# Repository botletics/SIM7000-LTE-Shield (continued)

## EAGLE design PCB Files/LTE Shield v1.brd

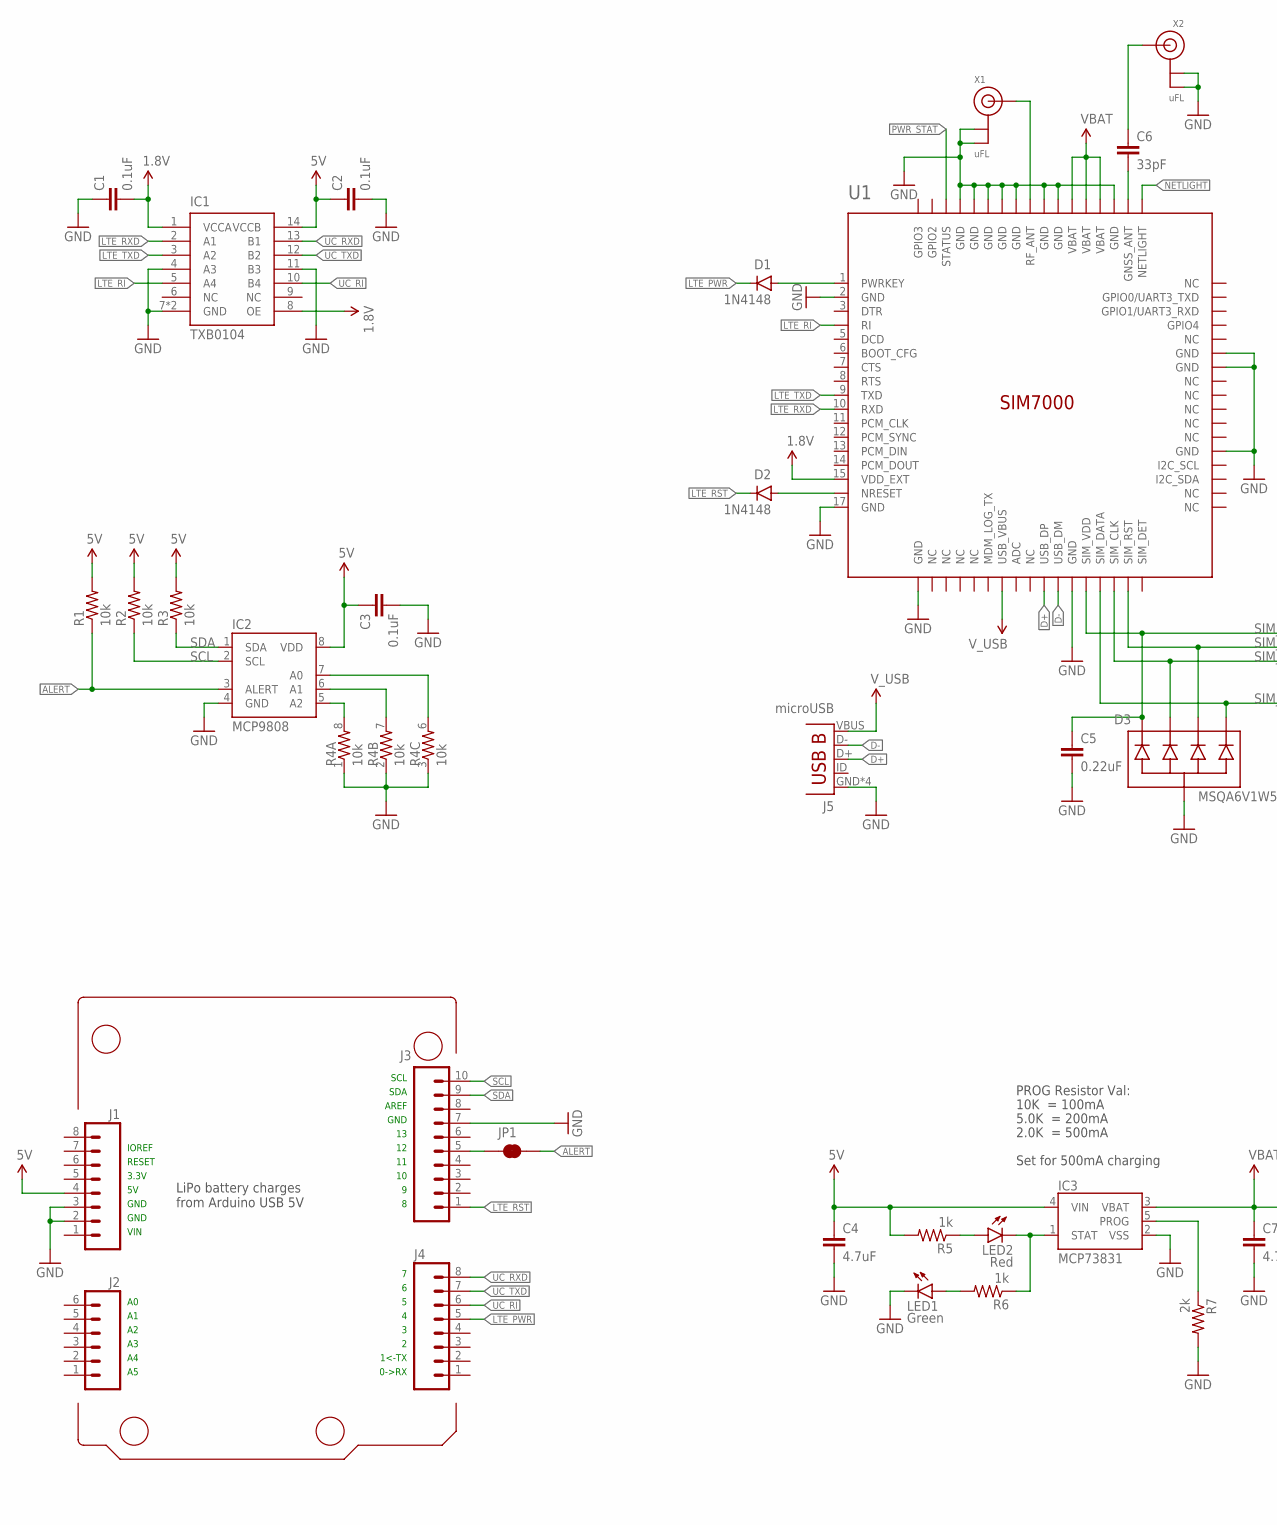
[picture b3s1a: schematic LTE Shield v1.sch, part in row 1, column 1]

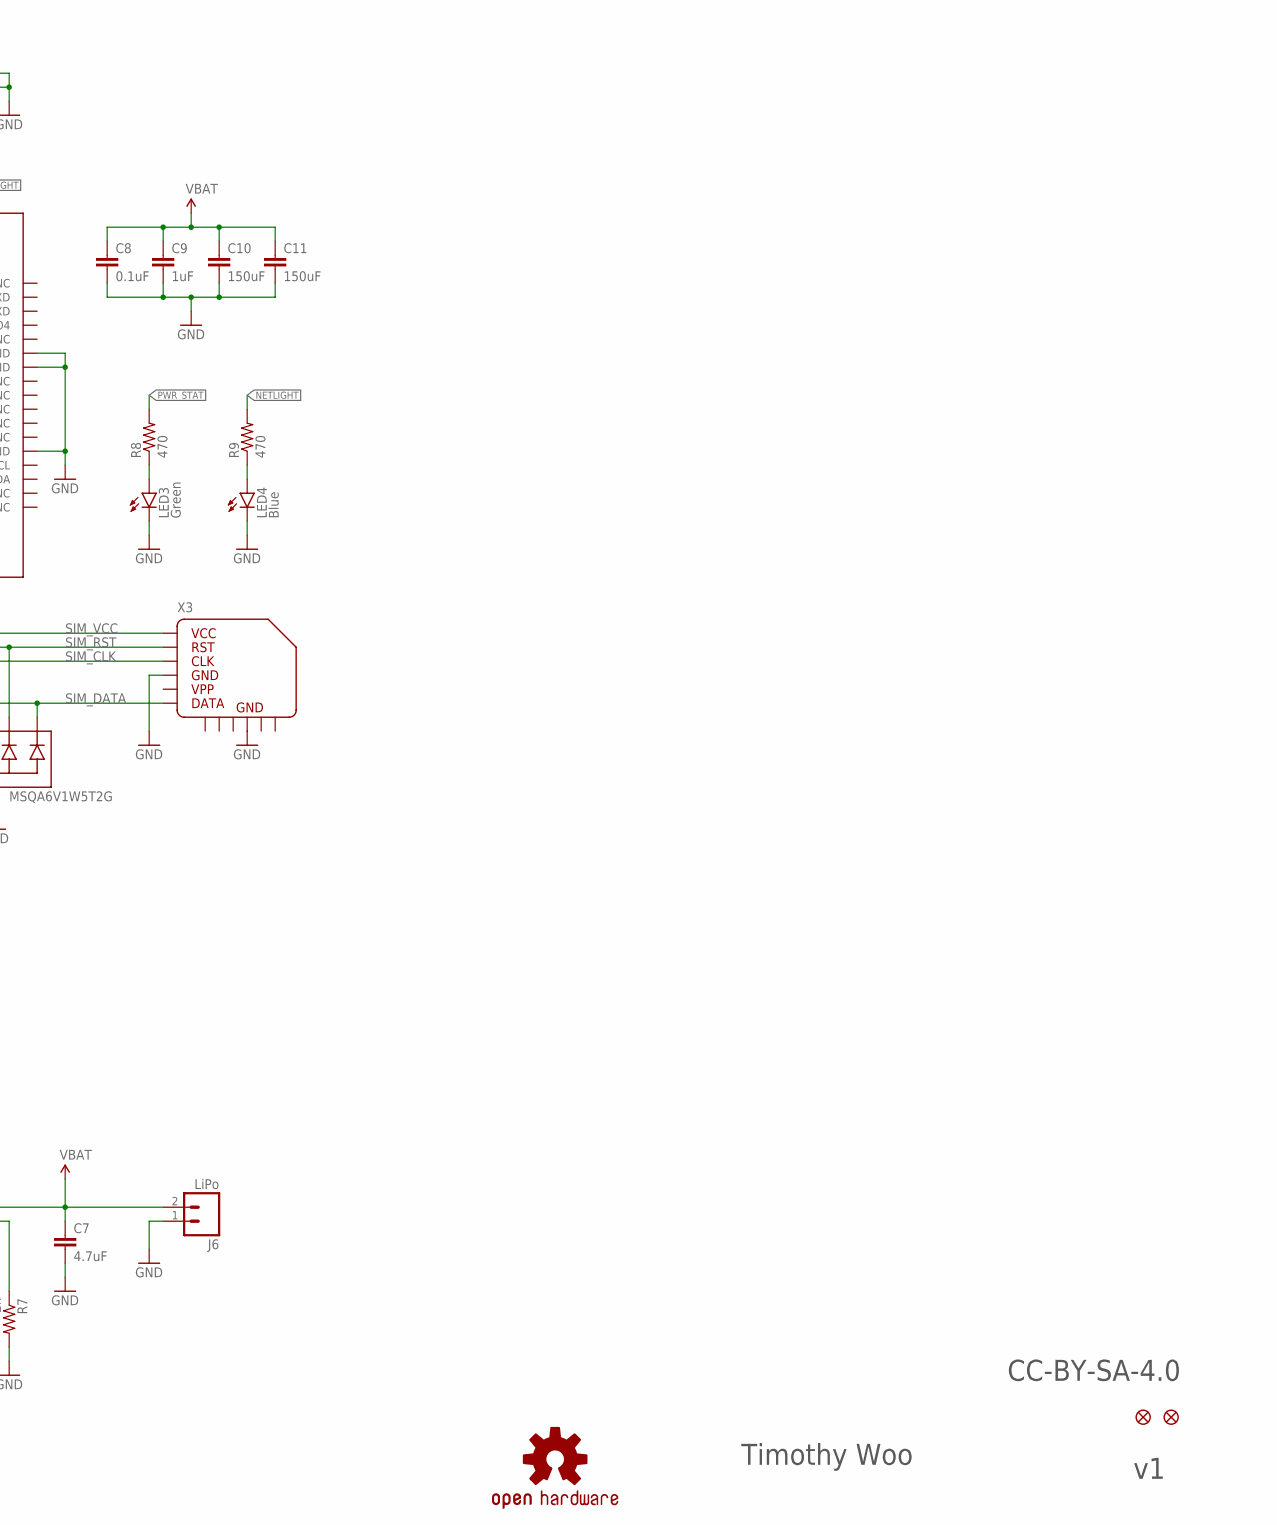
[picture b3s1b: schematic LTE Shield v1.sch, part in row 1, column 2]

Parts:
C1, C2, C3, C8: 0.1uF; 0603-CAP-MARKED
C4, C7: 4.7uF; 0603-CAP-MARKED
C5: 0.22uF; 0603-CAP-MARKED
C6: 33pF; 0603-CAP-MARKED
C9: 1uF; 0603-CAP-MARKED
C10, C11: 150uF; 1206
D1, D2: 1N4148; SOD-323
D3: MSQA6V1W5T2G; SOT-353
FID1, FID2: FIDUCIAL; FIDUCIAL_1MM
IC1: TXB0104; VQFN-14
IC2: MCP9808; 8-TSSOP
IC3: MCP73831; SOT23-5
J1, J4: M08SILK_PTH; 1X08
J2: M06SILK_PTH; 1X06
J3: M10SILK_PTH; 1X10
J5: microUSB; USB-B-MICRO-SMD
J6: LiPo; JST-2-SMD
JP1: JUMPER-SMT_2_NC_TRACE_SILK; SMT-JUMPER_2_NC_TRACE_SILK
LED1, LED3: Green; LED-0603-MARKED
LED2: Red; LED-0603-MARKED
LED4: Blue; LED-0603-MARKED
LOGO1: OSHW-LOGOL; OSHW-LOGO-L
R1, R2, R3: 10k; 0603-RES-MARKED
R4: 10k; RES_ARRAY_4X0603
R5, R6: 1k; 0603-RES-MARKED
R7: 2k; 0603-RES-MARKED
R8, R9: 470; 0603-RES-MARKED
U1: SIM7000
X1, X2: uFL; U.FL
X3: MICROSIM_SOCKET_PUSH-PULL

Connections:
1.8V: C1.2, IC1.1 (VCCA), IC1.8 (OE), U1.15 (VDD_EXT)
5V: C2.1, C3.1, C4.1, IC1.14 (VCCB), IC2.8 (VDD), IC3.4 (VIN), J1.4, R1.2, R2.2, R3.2, R5.2
ADDR0: IC2.7 (A0), R4.6 (2)
ADDR1: IC2.6 (A1), R4.7 (2)
ADDR2: IC2.5 (A2), R4.8 (2)
ALERT: IC2.3 (ALERT), JP1.2, R1.1
D+: J5.D+, U1.27 (USB_DP)
D-: J5.D-, U1.28 (USB_DM)
GND: C1.1, C2.2, C3.2, C4.2, C5.2, C7.2, C8.2, C9.2, C10.2, C11.2, D3.2 (COM), IC1.4 (A3), IC1.7 (GND), IC1.11 (B3), IC1.PAD (GND), IC2.4 (GND), IC3.2 (VSS), J1.2, J1.3, J3.7, J5.GND, J5.SHIELD1 (GND), J5.SHIELD2 (GND), J5.SHIELD3 (GND), J6.1 (2), LED1.C, LED3.C, LED4.C, R4.1, R4.2 (1), R4.3 (1), R7.2, U1.2 (GND), U1.17 (GND), U1.18 (GND), U1.29 (GND), U1.39 (GND), U1.45 (GND), U1.46 (GND), U1.54 (GND), U1.58 (GND), U1.59 (GND), U1.61 (GND), U1.62 (GND), U1.63 (GND), U1.64 (GND), U1.65 (GND), X1.1 (GND), X1.2 (GND), X2.1 (GND), X2.2 (GND), X3.C5, X3.GND@1 (GND), X3.GND@2 (GND), X3.GND@3 (GND), X3.GND@4 (GND), X3.GND@5 (GND), X3.GND@6 (GND)
LTE_PWR: D1.C, J4.5
LTE_RI: IC1.5 (A4), U1.4 (RI)
LTE_RST: D2.C, J3.1
LTE_RXD: IC1.2 (A1), U1.10 (RXD)
LTE_TXD: IC1.3 (A2), U1.9 (TXD)
unnamed: C6.2, U1.53 (GNSS_ANT)
unnamed: D1.A, U1.1 (PWRKEY)
unnamed: C6.1, X2.3 (SIGNAL)
unnamed: LED3.A, R8.1
unnamed: LED4.A, R9.1
unnamed: LED2.A, R5.1
unnamed: J3.5, JP1.1
unnamed: LED1.A, R6.2
NETLIGHT: R9.2, U1.52 (NETLIGHT)
NRESET: D2.A, U1.16 (NRESET)
PROG: IC3.5 (PROG), R7.1
PWR_STAT: R8.2, U1.66 (STATUS)
RF_ANT: U1.60 (RF_ANT), X1.3 (SIGNAL)
SCL: IC2.2 (SCL), J3.10, R2.1
SDA: IC2.1 (SDA), J3.9, R3.1
SIM_CLK: D3.3 (2), U1.32 (SIM_CLK), X3.C3
SIM_DATA: D3.5 (4), U1.31 (SIM_DATA), X3.C7
SIM_RST: D3.4 (3), U1.33 (SIM_RST), X3.C2
SIM_VCC: C5.1, D3.1, U1.30 (SIM_VDD), X3.C1
STAT: IC3.1 (STAT), LED2.C, R6.1
UC_RI: IC1.10 (B4), J4.6
UC_RXD: IC1.13 (B1), J4.8
UC_TXD: IC1.12 (B2), J4.7
VBAT: C7.1, C8.1, C9.1, C10.1, C11.1, IC3.3 (VBAT), J6.2 (1), U1.55 (VBAT), U1.56 (VBAT), U1.57 (VBAT)
V_USB: J5.VBUS, U1.24 (USB_VBUS)

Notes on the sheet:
Set for 500mA charging
10K = 100mA
5.0K = 200mA
2.0K = 500mA
PROG Resistor Val:
IOREF
3.3V
RESET
GND
VIN
0->RX
1<-TX
AREF
SDA
SCL
LiPo battery charges from Arduino USB 5V
Timothy Woo
CC-BY-SA-4.0

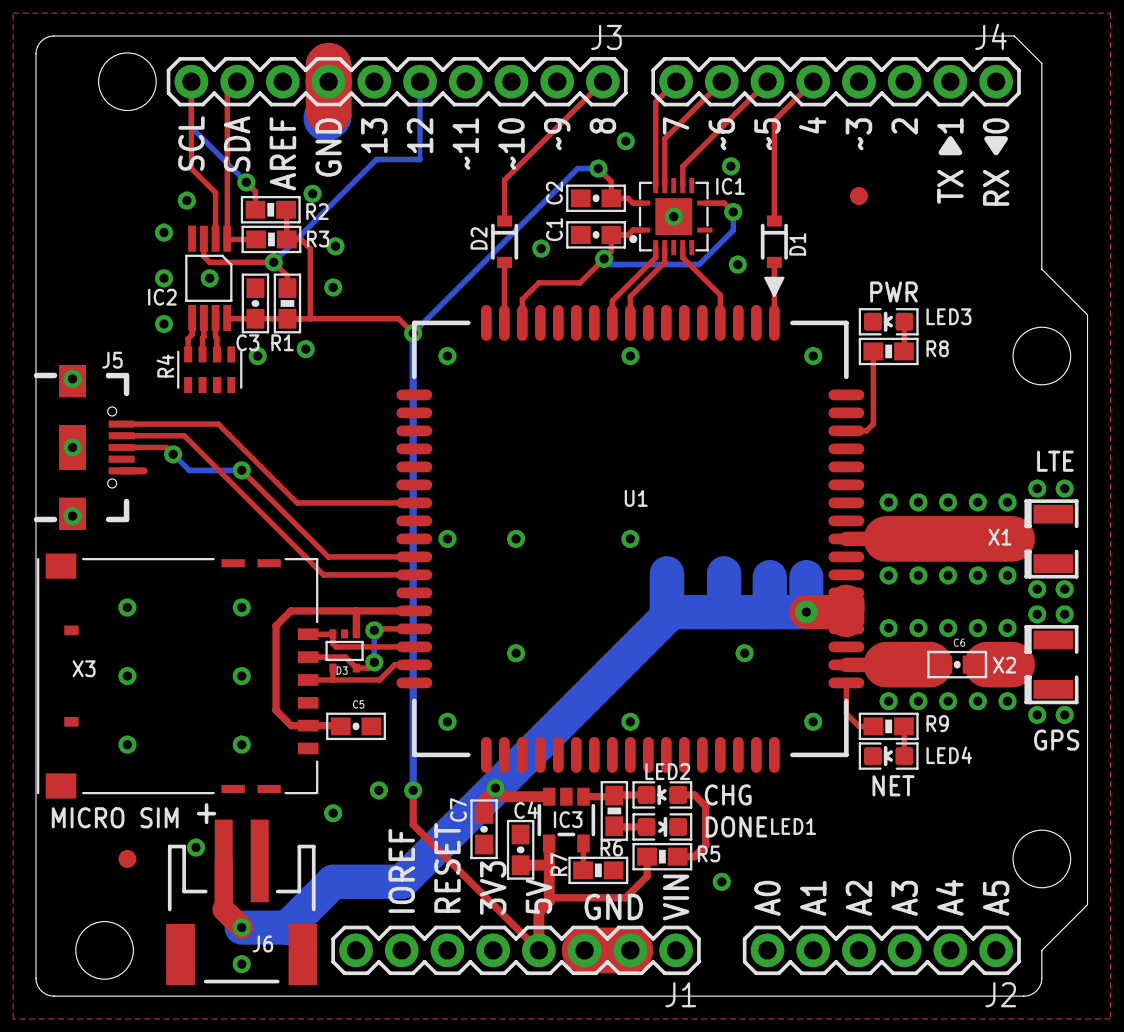
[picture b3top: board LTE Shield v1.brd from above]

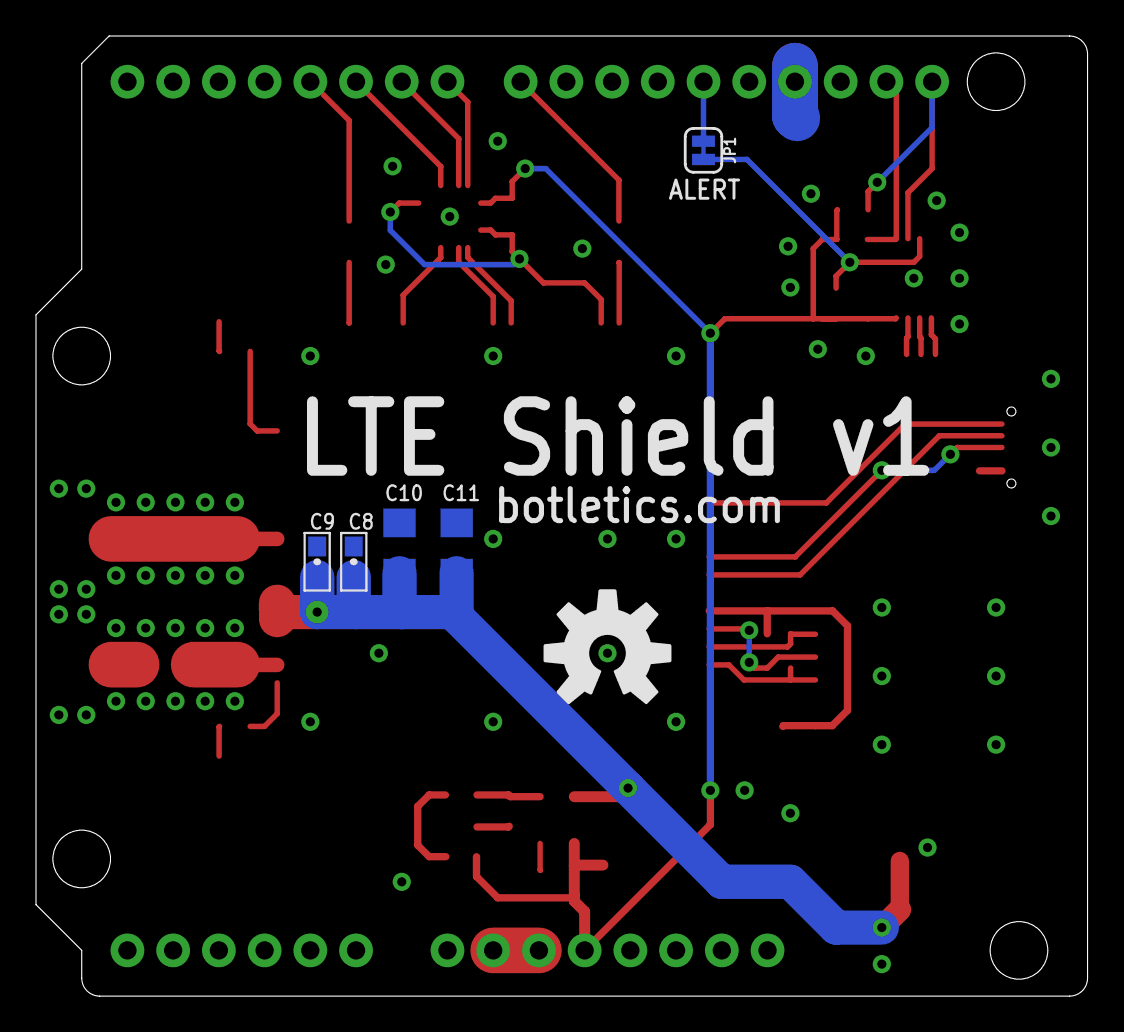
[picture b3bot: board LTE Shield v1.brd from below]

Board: 2 copper layers, 58.4 x 53.3 mm, 44 parts (6 on the bottom side), 39 nets.

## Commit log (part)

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2018-10-05 Fixed bugs in FTP functions
2018-10-17 Changed 4800 to 9600 baud
2018-10-17 Changed from 4800 to 9600 baud
2018-10-18 Changed serial port def for SAMD boards
2018-10-18 Added delay for HTTP POST
    Needed for high baud rates like 115200 baud with ATSAMD21 hardware serial. Would error out without the delay after "DOWNLOAD" was received.
2018-10-21 Got rid of unnecessary "replybuffer[]"
2018-10-21 Got rid of unnecessary "replybuffer"
2018-10-21 Added short delay after AT+IPR command
2018-10-21 Added short delay after AT+IPR
2018-10-22 Fixed and tested FTP functions (in progress)
2018-10-22 Tested FTP
2018-10-22 Fixed and tested FTP (ongoing)
2018-10-22 Fixed FTP delete method
    SIMCom FTP app note has wrong command. It shows AT+FTPDELE=1 but really it should just be AT+FTPDELE
2018-10-23 Fixed double AT+GNSINF command for getGPS()
2018-10-27 Added more functions
    Added enableSleepMode(), set_eDRX(), enablePSM() and setNetLED() methods
2018-10-27 Added function examples (commented)
    Lines 209-219
2018-10-29 Fixed compile warnings
2018-11-05 Set AT+CFUN=1 and PDP params
    Ensures module will connect without user manually setting it
2018-11-05 Set AT+CFUN=1 and PDP context
2018-11-05 Set PDP context in setNetworkSettings() method
2018-11-12 Added ESP8266 pin definitions
2018-11-12 Added SAMD21 serial definition
2018-11-12 Added SAMD serial definition
2018-11-27 Fixed ESP8266 v2.4.x compile errors
2018-11-27 Deleted ESP8266 v2.3.0 rollback statement
2018-11-27 Optimized for less memory
2018-11-28 No longer needed
    Initialization code in examples takes care of baud rate setting.
2018-11-28 No longer needed
    Use serial passthrough ("S" command) in LTE_Demo.ino instead
2018-12-07 Change debug serial baud to 9600
    115200 makes output become garbled in serial monitor.
2018-12-07 Lower debug serial baud rate
2018-12-07 Change sketch name serial printout
2018-12-09 Add config functions to LTE class
    Add setPreferredMode(), setPreferredLTEMode(), and setOperatingBand() functions.
2018-12-09 Fix setOperatingBand() error
2018-12-09 Add commented LTE functions after module init
2018-12-10 Use CGREG instead of CREG for SIM7000/7500
2018-12-16 Fix bunch of little things
2018-12-18 Fix small typo
2018-12-27 Replace enableNetworkTimeSync with enableRTC
2018-12-27 Replace enableNetworkTimeSync with enableRTC()
2019-01-16 Remove Adafruit 'w' and 'W' commands for 3G
2019-01-18 Update postData() function
2019-02-14 Add new SIM7000E firmware revision
2019-07-02 Update Adafruit_FONA.cpp
    I don't know if this might be an appropriate solution but I tried to replace the lines that gave me the errors reported in the following topic https://github.com/botletics/SIM7000-LTE-Shield/issues/1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
2019-07-22 Fix setNetLED() function mistake
2019-07-22 Add battery topic
2019-07-22 Add SIM7000 MQTT functions
2019-07-22 Add MQTT functions
    - openWirelessConnection() function using AT+CNACT command
    - wirelessConnStatus() function using AT+CNACT?
    - MQTTsetParameter() function using AT+SMCONF
    - MQTTconnect() function using AT+SMCONN and AT+SMDISC
    - MQTTconnectionStatus() function using AT+SMSTATE?
    - MQTTsubscribe() function using AT+SMSUB
2019-07-22 MQTT function name changes
    Add underscores after "MQTT" in function names for the LTE class functions.
2019-07-22 Change MQTT function names
2019-07-24 Tested SIM7000 MQTT functions
    Subscribe feature does not seem to work on 1351B03SIM7000A firmware using CloudMQTT
2019-07-24 Test with CloudMQTT
2019-07-25 Rename readme.txt to README.md
2019-08-01 Add SIM7600 support
2019-08-01 Add Ubidots demo for SIM5320
2019-08-05 Add MQTT subscribe message reading and parsing
2019-09-24 Add TLS layer for TCP
2020-01-29 Comment out temp sensor wake line
2020-01-29 Add MCP9808 address in tempsensor.begin()
2020-04-20 added deleteAllSMS method
2020-04-20 removing extra newline chars in outgoing SMS
2020-04-20 Fix MQTT protocol name length
2020-05-21 Fix MQTT packet length definition
2020-11-04 Fix eDRX
    eDRX_val has to be sent in string
2020-11-04 Add PSM custom TAU and active time
    Without providing the values, PSM will adopt adopt manufacturer default values or previously configured values.
2020-12-15 Update Adafruit_FONA.h
    update readRTC() function
2020-12-15 Update Adafruit_FONA.cpp
    update readRTC() function
2021-01-06 Decrease MQTT_publish getReply() time
2021-01-07 Add SSL to TCP functions
2021-01-07 Add SIM7070 support
2021-01-07 Edit callPhone() function for SIM7000/7070
2021-01-07 Remove SIM7000/7070/7X00 _type variants
    Still supports legacy code
2021-01-07 Remove SIM7000/7070/7X00 _type variants
2021-01-07 Remove specific module variants
2021-01-07 Add powerOn() function
2021-01-07 Use library powerOn() function
2021-01-07 Use library powerOn() function and add SIM7070
2021-01-07 Fix bug
2021-01-07 Remove separate dtostrf emulation code
2021-01-08 SSL bug fix
2021-01-08 SIM7070 postData() updates
    Still incomplete
2021-01-08 SIM7070 HTTP GET and POST
2021-01-10 Hardware serial example
2021-01-23 Increase sendSMS wait time
2021-01-27 Update Adafruit_FONA.cpp
    updated wirelessConnStatus() for SIM7070
2021-01-27 Update HTTP functions for SIM7070
2021-01-27 Update SIM7070 HTTP example
2021-01-29 Increase SMS verification wait time
2021-01-30 Update SIM7070 functions
2021-01-30 Change for SIM7070
2021-02-19 Fix powerOn() delay typo
2021-03-23 Fix syntax typo
2021-03-27 Change default to HTTP GET
2021-03-31 Fix module type definition for getNetworkStatus()
2021-03-31 Fix power on logic
2021-04-09 Fix readSMS index for SIM7000
2021-04-10 Update Adafruit_FONA.cpp
    Some generic eBay boards seem to use a different revision / firmware of the 808 chip that is detected slightly differently - its still an 808 chip, but has the bluetooth and other bits enabled. I wil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
2021-04-24 Add DNS lookup, UDP connect and longer network info
    Added commands for DNS lookup and opening UDP connections. Added Test command for AT+COPS=?
2021-04-24 Increase MQTT cmdStr buffer size
2021-05-04 Fixes per PlatformIO static analysis
2021-05-15 Update +CHTTPSOPSE check for SIM7500E rev1.1 FW
2021-06-13 Removing a warning/error. The sprintf function when %lu is specified expects a "long unsigned int" but the argument supplied was a uint32_t {aka unsugned int}. In this case the argument actually is a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
2021-06-13 Correct an actual bug. The warning was: "comparison is always false due to limited range of data type". The variable remBytes was declared as a uint16_t but then compared to a const of 300000 which i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
    Really I would recomend replacing the 6 "300000" with a const
    uint32_t offsetSize = 300000 and then use the const variable in the 6
    locations much less error prone in the long term.
2021-06-13 Remove some warnings so that it's easier to see real issues when doing a build. Chunks of code are commented out when not doing specific things.
    If you don't care about UTC time all of the serial print statements are
    commented out but the declaration of the used variables are not commented
    out generating an un-needed warning.
    Likewise if you are not going to use the HTTP POST method to dweet.io the
    code is commented out but the declaration of the variable "body" is not
    commented out again generating an un-needed warning.
2021-07-31 Eat OK reply after getNetworkInfo()
2022-01-28 Workaround for race condition in postData. Timeout for AT command needs to be lower than timeout in sendCheckReply
2022-01-28 Fixed possible buffer overflow in readline
2022-01-28 Fixed compiler warnings
    Removed String conversions in favor of C-functions with less overhead
2022-01-28 Add function to query status of NTP module - getNTPstatus
2022-01-28 Added method for checking SIM PIN requirement
2022-01-28 Changed setBaudrate variable type to allow baud rates >65K (e.g. 115200)
2022-01-28 Added getNetworkType to query whether the module is connected to GSM, LTE, etc.
2022-01-28 Added getIPv4 to get the IP of the modem as a string
2022-01-28 Added getBearerStatus to get whether the modem is connected to a bearer or not
2022-01-28 Fixed missing header change
2022-01-28 Changed all timeout variables to be uint32_t to allow for timeouts >65s (as required by the spec in some cases)
2022-01-28 Changed timeout for connecting/disconnecting to bearer according to spec
    Max response time according to AT-Command Manual v1.04 is 85s for connecting and 65s for disconnecting (see p.133)
2022-02-06 Read MQTT subscriptions
2022-03-02 Increase MQTT_publish cmdStr buffer
2022-03-02 Increase MQTT_subscribe cmdStr buffer
2022-06-12 Revert "Timeout fixes"
2022-06-14 Revert "Revert "Timeout fixes""
2022-06-14 Revert "Revert "Revert "Timeout fixes"""
2022-07-05 Update MQTT_setParameter()
2022-07-05 See new file SIM70X0_MQTT_Demo
2022-07-05 Add 'D' option to menu
2022-07-05 Fix temp sensor wake logic
2022-07-11 Fix for ESP32 compile
2022-09-01 Add AT+SHSSL command for SSL
2022-09-08 Add SSL to HTTP_connect()
2022-10-31 Updated library.properties for Botletics.
2022-10-31 Rearranged in accordance with Arduino library.
2022-10-31 Moved library.properties to root.
2022-10-31 Remove code (see new repo)
    https://github.com/botletics/SIM7000-Shield-Library
2022-10-31 Update README's
2022-11-02 Repointed Code to new repo location.
